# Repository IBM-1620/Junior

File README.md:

# Junior
A project sponsored by the Computer History Museum to recreate the experience (visual, auditory, tactile, visceral) of running historic software on a 1960s-era computer.

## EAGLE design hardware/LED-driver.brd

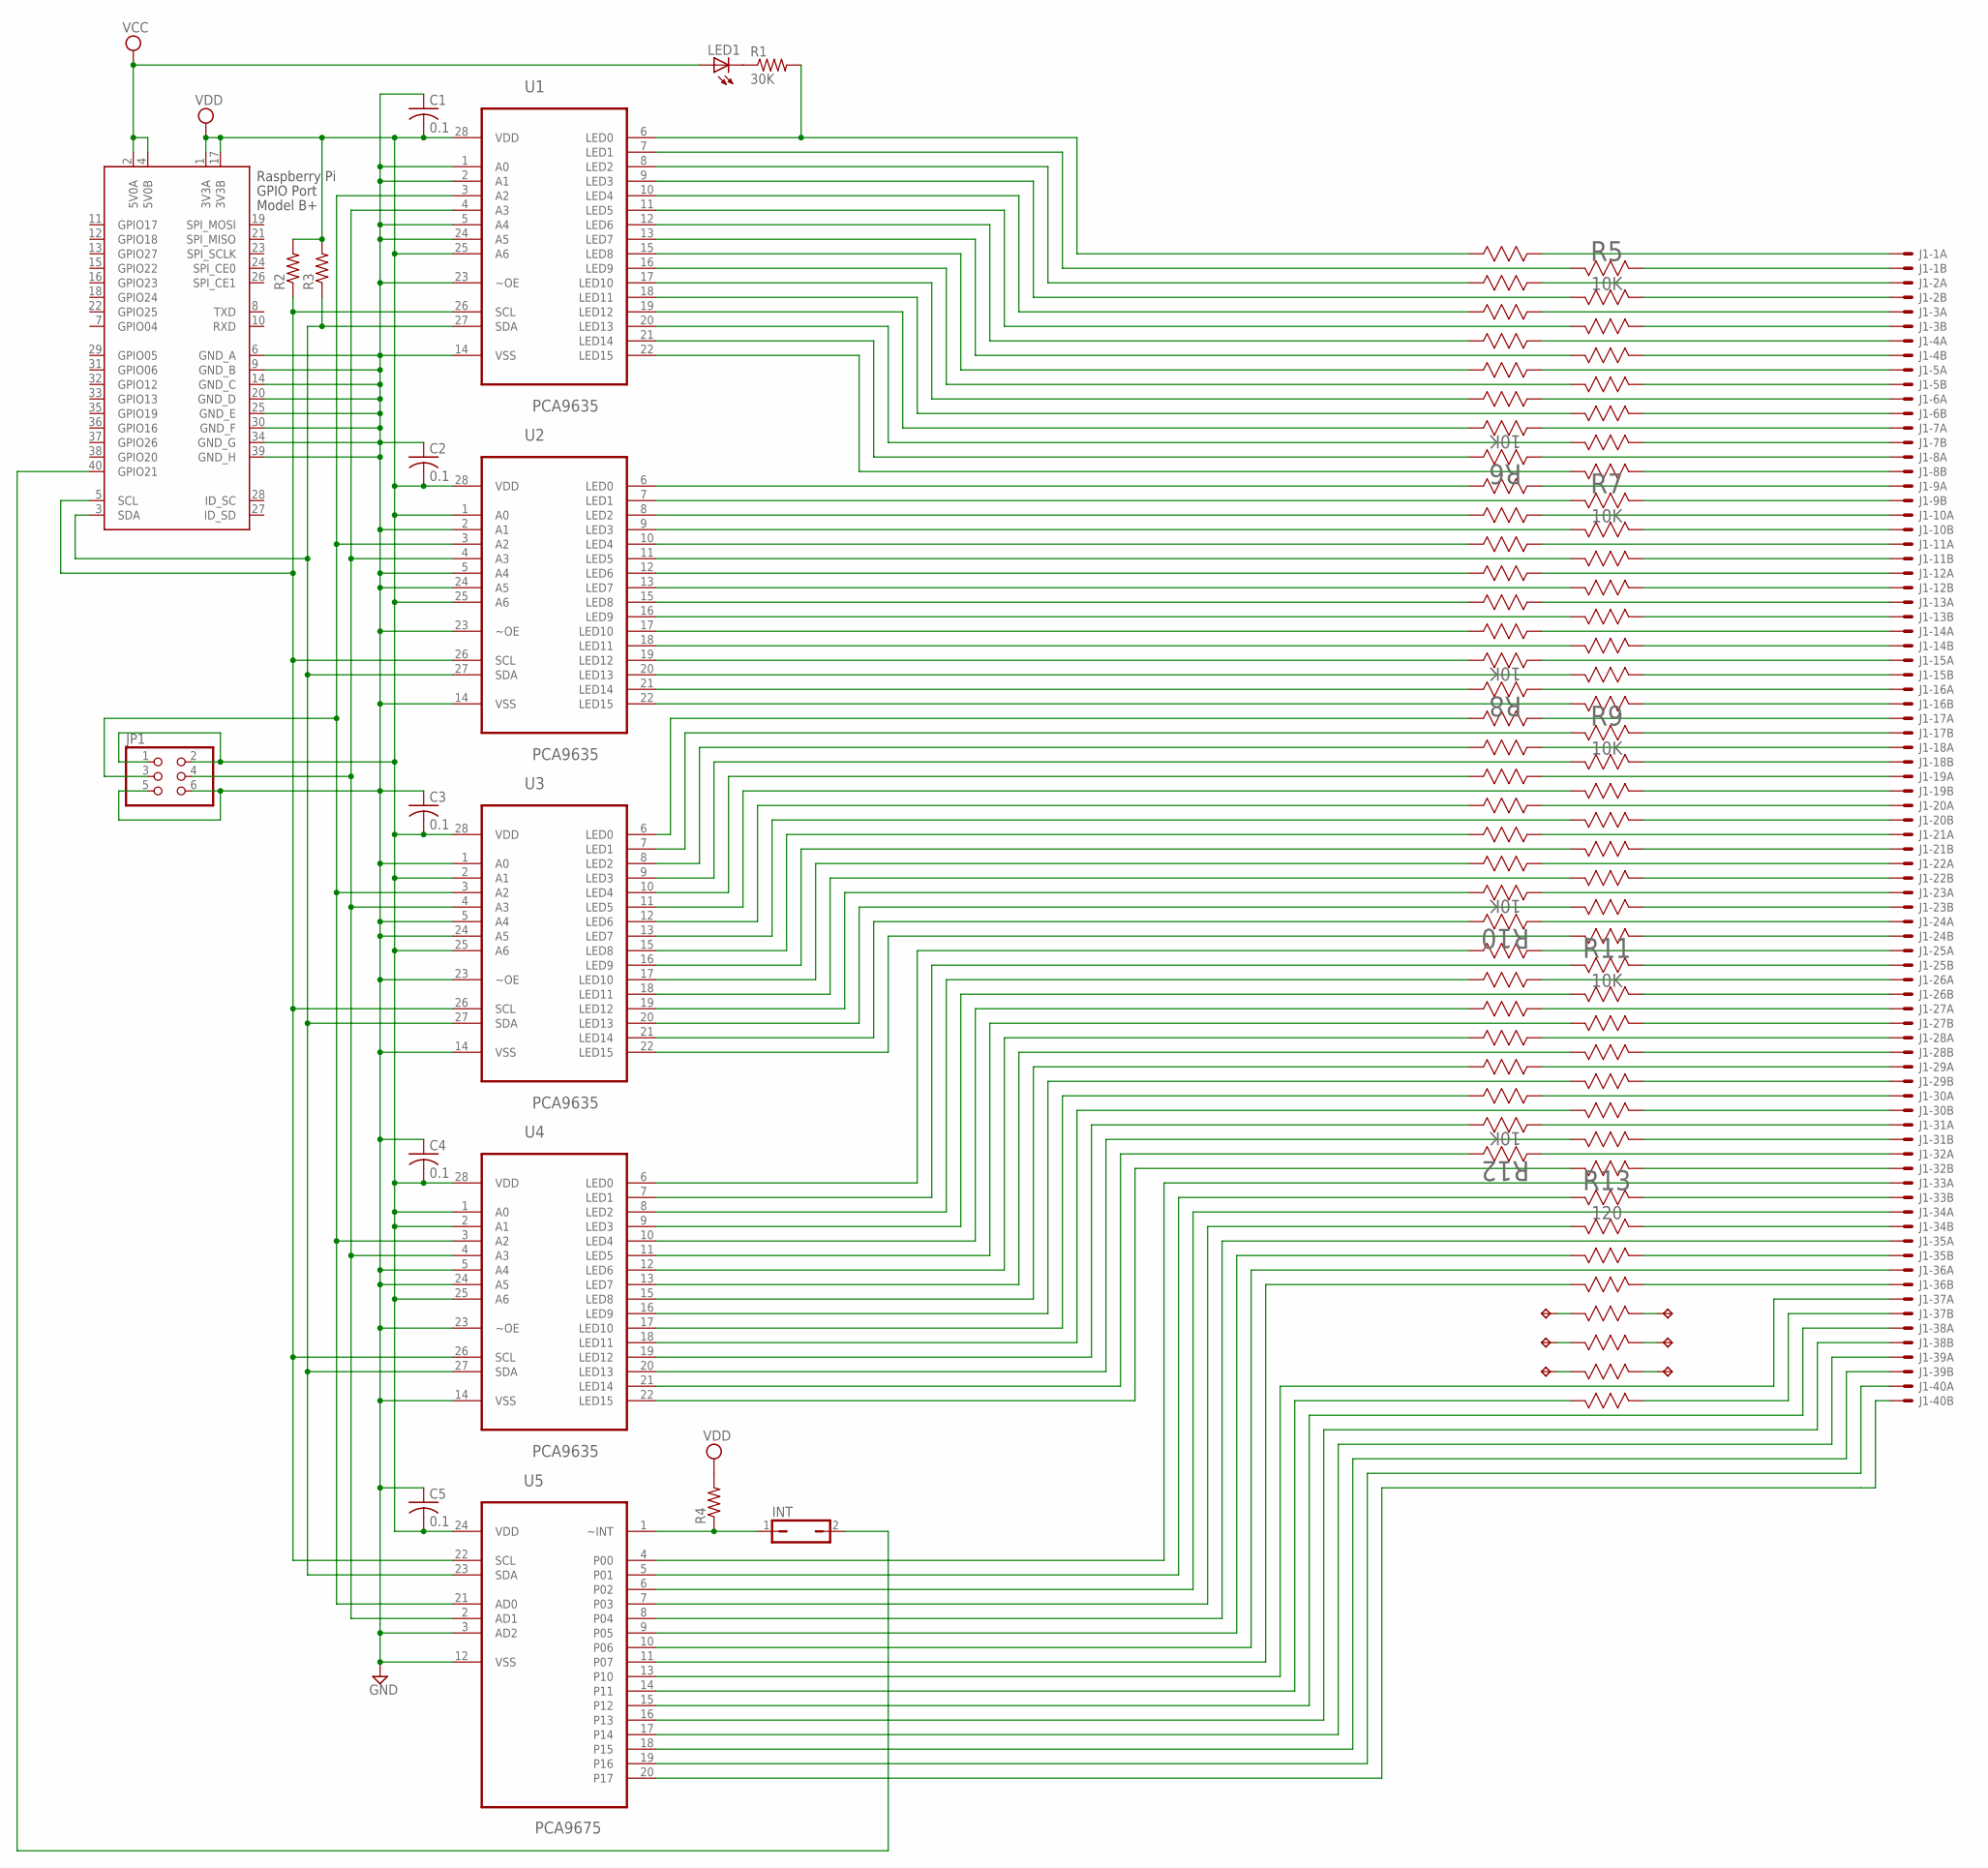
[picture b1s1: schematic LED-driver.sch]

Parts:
C1, C2, C3, C4, C5: 0.1; C025-030X050
INT: JP1Q; JP1
J1: CON-80-EDGE; CARDEDGE-80
JP1: JUMPER-3X2; 3X2
LED1: LED5MM
R1: 30K; 0207/10
R2, R3, R4: R-US_0207/10; 0207/10
R5, R6, R7, R8, R9, R10, R11, R12: 10K; SOMC16-M
R13: 120; SOMC16-M
TP1, TP2, TP3, TP4, TP5, TP6: TP
U1, U2, U3, U4: PCA9635; SOP65P640X110-28N
U5: PCA9675; SOP65P640X110-24N
X1: RASPI_BOARD_B+#_E4; RASPI_BOARD_B+_EDGES_4DRILL

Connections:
GND: C1.1, C2.1, C3.1, C4.1, C5.1, JP1.5, JP1.6, U1.1 (A0), U1.2 (A1), U1.5 (A4), U1.14 (VSS), U1.23 (~OE), U1.24 (A5), U2.2 (A1), U2.5 (A4), U2.14 (VSS), U2.23 (~OE), U2.24 (A5), U3.1 (A0), U3.5 (A4), U3.14 (VSS), U3.23 (~OE), U3.24 (A5), U4.5 (A4), U4.14 (VSS), U4.23 (~OE), U4.24 (A5), U5.3 (AD2), U5.12 (VSS), X1.6 (GND_A), X1.9 (GND_B), X1.14 (GND_C), X1.20 (GND_D), X1.25 (GND_E), X1.30 (GND_F), X1.34 (GND_G), X1.39 (GND_H)
unnamed: R1.2, R6.9 (916), U1.6 (LED0)
unnamed: R5.16 (162), U1.7 (LED1)
unnamed: R6.10 (1014), U1.8 (LED2)
unnamed: R5.15 (154), U1.9 (LED3)
unnamed: R6.11 (1112), U1.10 (LED4)
unnamed: R5.14 (146), U1.11 (LED5)
unnamed: R6.12 (1210), U1.12 (LED6)
unnamed: R5.13 (138), U1.13 (LED7)
unnamed: R6.13 (138), U1.15 (LED8)
unnamed: R5.12 (1210), U1.16 (LED9)
unnamed: R6.14 (146), U1.17 (LED10)
unnamed: R5.11 (1112), U1.18 (LED11)
unnamed: R6.15 (154), U1.19 (LED12)
unnamed: R5.10 (1014), U1.20 (LED13)
unnamed: R6.16 (162), U1.21 (LED14)
unnamed: R5.9 (916), U1.22 (LED15)
unnamed: J1.36A, U5.10 (P06)
unnamed: R3.1, U1.27 (SDA), U2.27 (SDA), U3.27 (SDA), U4.27 (SDA), U5.23 (SDA), X1.3 (SDA)
unnamed: R8.9 (916), U2.6 (LED0)
unnamed: R2.1, U1.26 (SCL), U2.26 (SCL), U3.26 (SCL), U4.26 (SCL), U5.22 (SCL), X1.5 (SCL)
unnamed: R13.13 (138), U5.11 (P07)
unnamed: R7.16 (162), U2.7 (LED1)
unnamed: R8.10 (1014), U2.8 (LED2)
unnamed: R7.15 (154), U2.9 (LED3)
unnamed: R8.11 (1112), U2.10 (LED4)
unnamed: R7.14 (146), U2.11 (LED5)
unnamed: R8.12 (1210), U2.12 (LED6)
unnamed: R7.13 (138), U2.13 (LED7)
unnamed: R8.13 (138), U2.15 (LED8)
unnamed: R7.12 (1210), U2.16 (LED9)
unnamed: R8.14 (146), U2.17 (LED10)
unnamed: R7.11 (1112), U2.18 (LED11)
unnamed: R8.15 (154), U2.19 (LED12)
unnamed: R7.10 (1014), U2.20 (LED13)
unnamed: R8.16 (162), U2.21 (LED14)
unnamed: R7.9 (916), U2.22 (LED15)
unnamed: R10.9 (916), U3.6 (LED0)
unnamed: R9.16 (162), U3.7 (LED1)
unnamed: R10.10 (1014), U3.8 (LED2)
unnamed: R9.15 (154), U3.9 (LED3)
unnamed: R10.11 (1112), U3.10 (LED4)
unnamed: R9.14 (146), U3.11 (LED5)
unnamed: R10.12 (1210), U3.12 (LED6)
unnamed: R9.13 (138), U3.13 (LED7)
unnamed: R10.13 (138), U3.15 (LED8)
unnamed: R9.12 (1210), U3.16 (LED9)
unnamed: R10.14 (146), U3.17 (LED10)
unnamed: R9.11 (1112), U3.18 (LED11)
unnamed: R10.15 (154), U3.19 (LED12)
unnamed: R9.10 (1014), U3.20 (LED13)
unnamed: R10.16 (162), U3.21 (LED14)
unnamed: R9.9 (916), U3.22 (LED15)
unnamed: R12.9 (916), U4.6 (LED0)
unnamed: R11.16 (162), U4.7 (LED1)
unnamed: R12.10 (1014), U4.8 (LED2)
unnamed: R11.15 (154), U4.9 (LED3)
unnamed: R12.11 (1112), U4.10 (LED4)
unnamed: R11.14 (146), U4.11 (LED5)
unnamed: R12.12 (1210), U4.12 (LED6)
unnamed: R11.13 (138), U4.13 (LED7)
unnamed: R12.13 (138), U4.15 (LED8)
unnamed: R11.12 (1210), U4.16 (LED9)
unnamed: R12.14 (146), U4.17 (LED10)
unnamed: R11.11 (1112), U4.18 (LED11)
unnamed: R12.15 (154), U4.19 (LED12)
unnamed: R11.10 (1014), U4.20 (LED13)
unnamed: R12.16 (162), U4.21 (LED14)
unnamed: R11.9 (916), U4.22 (LED15)
unnamed: J1.33A, U5.4 (P00)
unnamed: R13.16 (162), U5.5 (P01)
unnamed: J1.34A, U5.6 (P02)
unnamed: R13.15 (154), U5.7 (P03)
unnamed: J1.35A, U5.8 (P04)
unnamed: R13.14 (146), U5.9 (P05)
unnamed: JP1.3, U1.3 (A2), U2.3 (A2), U3.3 (A2), U4.3 (A2), U5.21 (AD0)
unnamed: JP1.4, U1.4 (A3), U2.4 (A3), U3.4 (A3), U4.4 (A3), U5.2 (AD1)
unnamed: J1.37A, U5.13 (P10)
unnamed: R13.9 (916), U5.14 (P11)
unnamed: J1.38A, U5.15 (P12)
unnamed: J1.38B, U5.16 (P13)
unnamed: J1.39A, U5.17 (P14)
unnamed: J1.39B, U5.18 (P15)
unnamed: J1.40A, U5.19 (P16)
unnamed: J1.40B, U5.20 (P17)
unnamed: LED1.K (C), R1.1
unnamed: J1.1A, R6.8 (815)
unnamed: J1.2A, R6.7 (713)
unnamed: INT.1, R4.1, U5.1 (~INT)
unnamed: INT.2, X1.40 (GPIO21)
unnamed: J1.3A, R6.6 (611)
unnamed: J1.4A, R6.5 (59)
unnamed: J1.5A, R6.4 (47)
unnamed: J1.6A, R6.3 (35)
unnamed: J1.7A, R6.2 (23)
unnamed: J1.8A, R6.1 (11)
unnamed: J1.1B, R5.1 (11)
unnamed: J1.2B, R5.2 (23)
unnamed: J1.3B, R5.3 (35)
unnamed: J1.4B, R5.4 (47)
unnamed: J1.5B, R5.5 (59)
unnamed: J1.6B, R5.6 (611)
unnamed: J1.7B, R5.7 (713)
unnamed: J1.8B, R5.8 (815)
unnamed: J1.9B, R7.1 (11)
unnamed: J1.10B, R7.2 (23)
unnamed: J1.11B, R7.3 (35)
unnamed: J1.12B, R7.4 (47)
unnamed: J1.13B, R7.5 (59)
unnamed: J1.14B, R7.6 (611)
unnamed: J1.15B, R7.7 (713)
unnamed: J1.16B, R7.8 (815)
unnamed: J1.9A, R8.8 (815)
unnamed: J1.10A, R8.7 (713)
unnamed: J1.11A, R8.6 (611)
unnamed: J1.12A, R8.5 (59)
unnamed: J1.13A, R8.4 (47)
unnamed: J1.14A, R8.3 (35)
unnamed: J1.15A, R8.2 (23)
unnamed: J1.16A, R8.1 (11)
unnamed: J1.17B, R9.1 (11)
unnamed: J1.18B, R9.2 (23)
unnamed: J1.19B, R9.3 (35)
unnamed: J1.20B, R9.4 (47)
unnamed: J1.21B, R9.5 (59)
unnamed: J1.22B, R9.6 (611)
unnamed: J1.23B, R9.7 (713)
unnamed: J1.24B, R9.8 (815)
unnamed: J1.25B, R11.1 (11)
unnamed: J1.26B, R11.2 (23)
unnamed: J1.27B, R11.3 (35)
unnamed: J1.28B, R11.4 (47)
unnamed: J1.29B, R11.5 (59)
unnamed: J1.30B, R11.6 (611)
unnamed: J1.31B, R11.7 (713)
unnamed: J1.32B, R11.8 (815)
unnamed: J1.33B, R13.1 (11)
unnamed: J1.34B, R13.2 (23)
unnamed: J1.35B, R13.3 (35)
unnamed: J1.36B, R13.4 (47)
unnamed: J1.37B, R13.8 (815)
unnamed: J1.17A, R10.8 (815)
unnamed: J1.18A, R10.7 (713)
unnamed: J1.19A, R10.6 (611)
unnamed: J1.20A, R10.5 (59)
unnamed: J1.21A, R10.4 (47)
unnamed: J1.22A, R10.3 (35)
unnamed: J1.23A, R10.2 (23)
unnamed: J1.24A, R10.1 (11)
unnamed: J1.25A, R12.8 (815)
unnamed: J1.26A, R12.7 (713)
unnamed: J1.27A, R12.6 (611)
unnamed: J1.28A, R12.5 (59)
unnamed: J1.29A, R12.4 (47)
unnamed: J1.30A, R12.3 (35)
unnamed: J1.31A, R12.2 (23)
unnamed: J1.32A, R12.1 (11)
unnamed: R13.12 (1210), TP1.1
unnamed: R13.11 (1112), TP2.1
unnamed: R13.10 (1014), TP3.1
unnamed: R13.5 (59), TP4.1
unnamed: R13.6 (611), TP5.1
unnamed: R13.7 (713), TP6.1
VCC: LED1.A, X1.2 (5V0A), X1.4 (5V0B)
VDD: C1.2, C2.2, C3.2, C4.2, C5.2, JP1.1, JP1.2, R2.2, R3.2, R4.2, U1.25 (A6), U1.28 (VDD), U2.1 (A0), U2.25 (A6), U2.28 (VDD), U3.2 (A1), U3.25 (A6), U3.28 (VDD), U4.1 (A0), U4.2 (A1), U4.25 (A6), U4.28 (VDD), U5.24 (VDD), X1.1 (3V3A), X1.17 (3V3B)

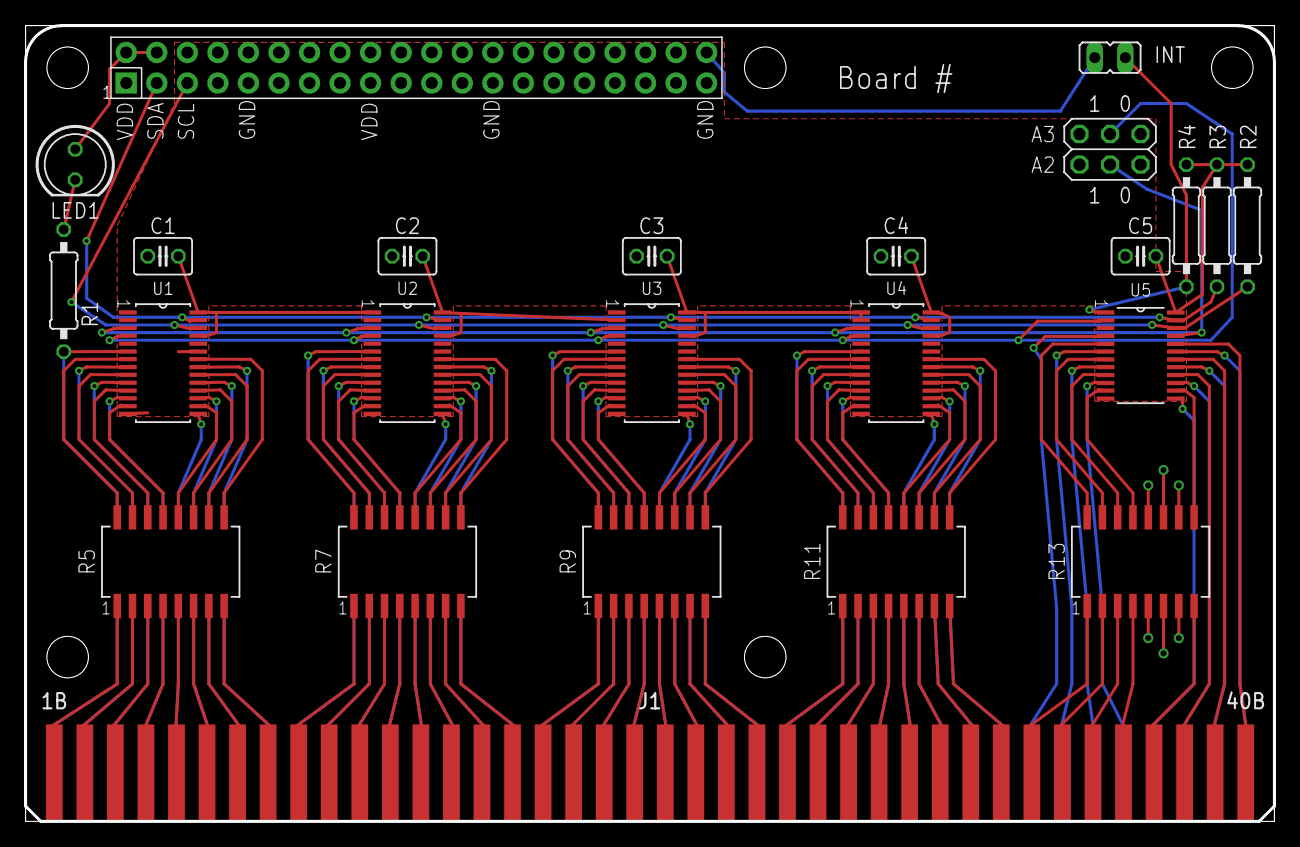
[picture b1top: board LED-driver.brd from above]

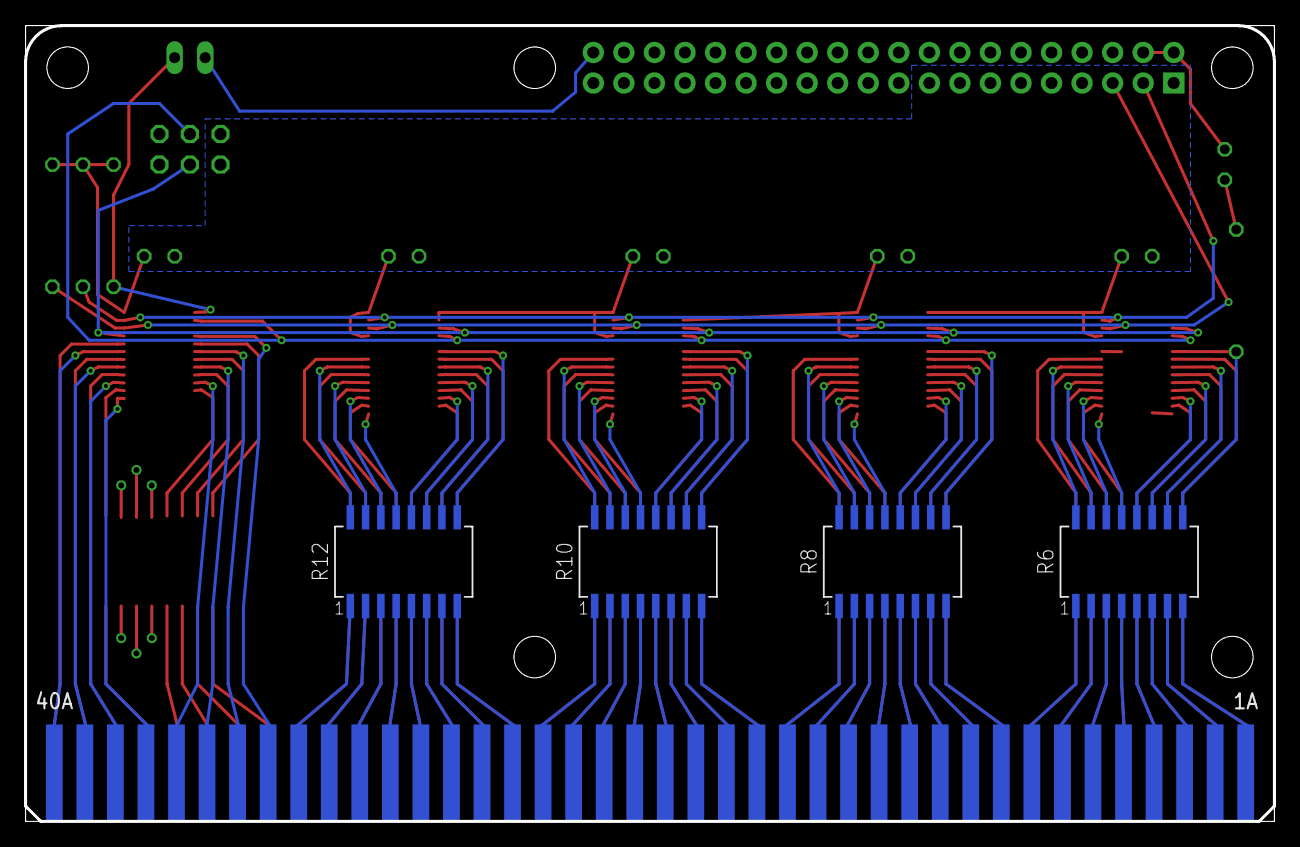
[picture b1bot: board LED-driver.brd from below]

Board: 2 copper layers, 103.8 x 66.2 mm, 34 parts (4 on the bottom side), 165 nets.

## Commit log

2018-07-24 Initial version of Wheelwriter 1000 Adaptation instructions.
2018-07-24 Add URL for accessing the document on github under the title.
2018-07-25 Initial posting of Wheelwriter Adaptation CAD diagram source and as printed with black background. Includes improved positioning of some dimensions and color adjustments.
2018-07-25 Ignore backup of CAD diagram.
2018-07-25 Add footer with page number and date; insert updated CAD diagram.
2020-09-15 A complete set of diagnostic test programs for the IBM 1620 Jr.
    Most of these programs are the original IBM 1620 diagnostics
    with the exception of CS01 and FP01 which were written for the
    IBM 1620 Jr.
    All of these programs are built into the simulator and can be
    loaded and run from the front panel following the directions
    in the IBM 1620 Jr Diagnostic Manual.
2020-09-17 Corrected font problem with Diagnostic Manual and improved document quality. Renamed IBM manuals. Minor updates to some cmem files.
2020-09-17 Updated file permissions.
2020-09-17 Added scanned diagnostic output files.
2020-09-17 Added Diagnostic Manual source file.
2020-10-29 Added project status reports.
2020-10-29 Better explained "power off".
2021-08-09 Provide EAGLE schematic and board layout for the LED Display board, plus a zip of Gerber files generated from that board layout. Three of these boards provide the connections to all the LED lights an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
